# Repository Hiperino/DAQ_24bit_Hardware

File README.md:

# DAQ_24bit
Simple 4 channel 24bit USB DAQ
Uses ADS122U04 ADC and MCP2200 UART/GPIO - USB converter. No Dedicated uC.
4 Input channels with 4 ranges (+- 1V, 2V, 10V, 25V) and 2 current output channels.

Project for fun and curiosity with a purpose to make a simple yte precise USB DAQ without a dedicated controller requireig firmware.

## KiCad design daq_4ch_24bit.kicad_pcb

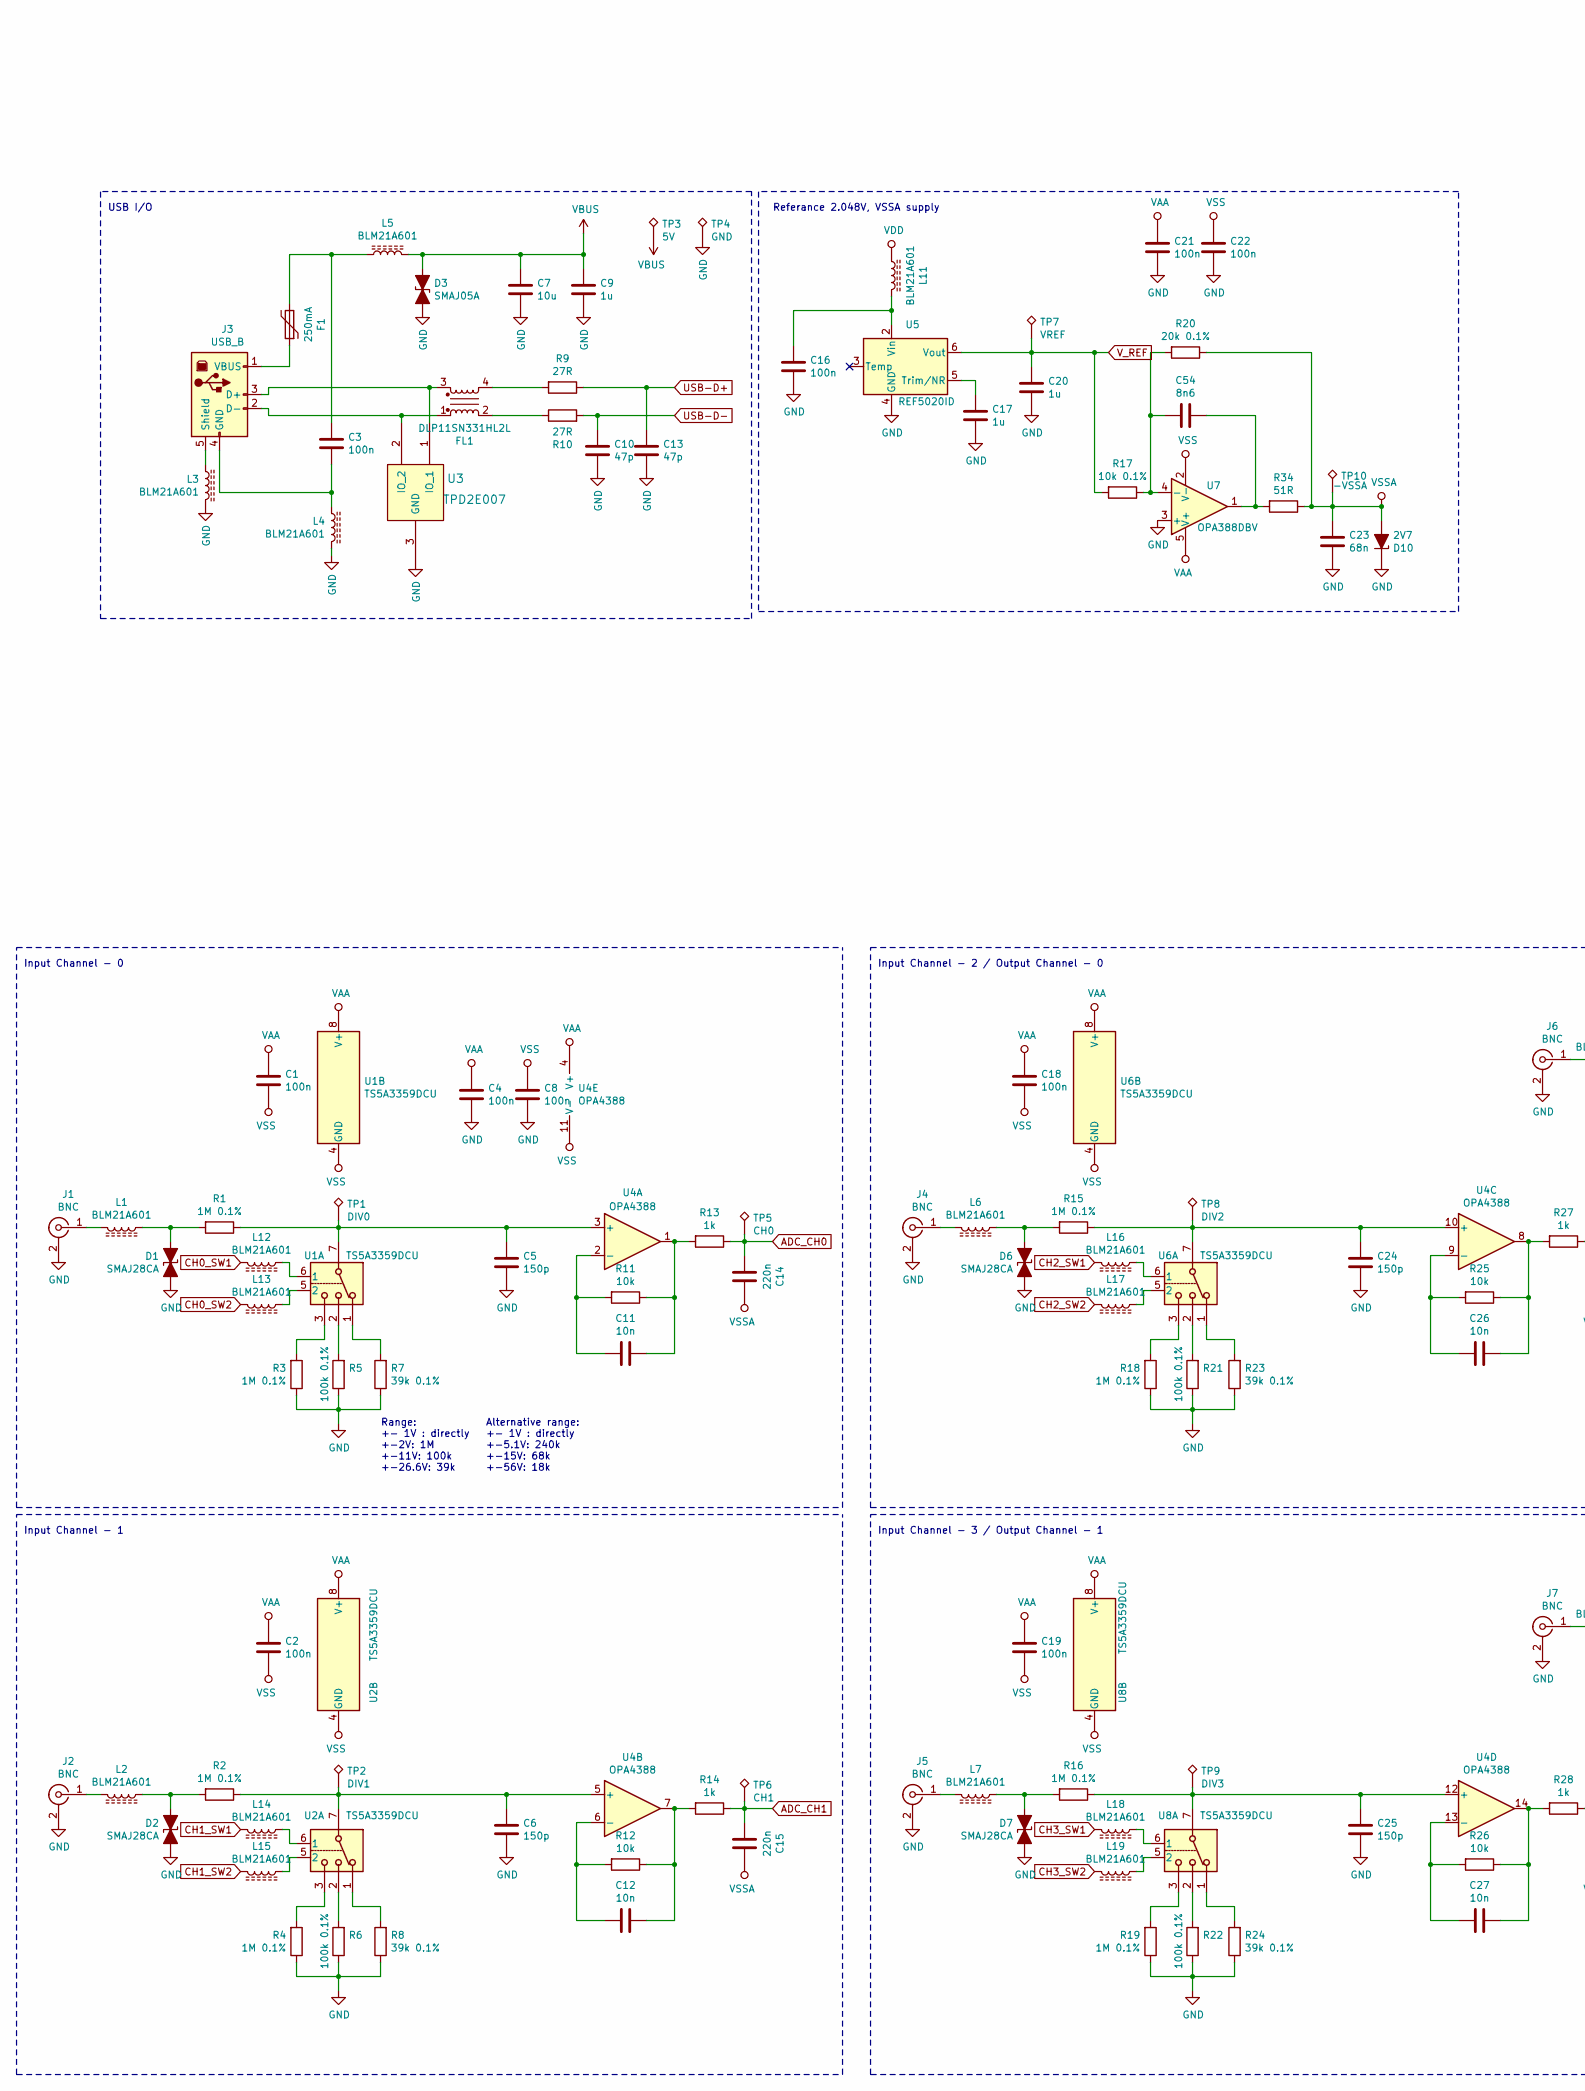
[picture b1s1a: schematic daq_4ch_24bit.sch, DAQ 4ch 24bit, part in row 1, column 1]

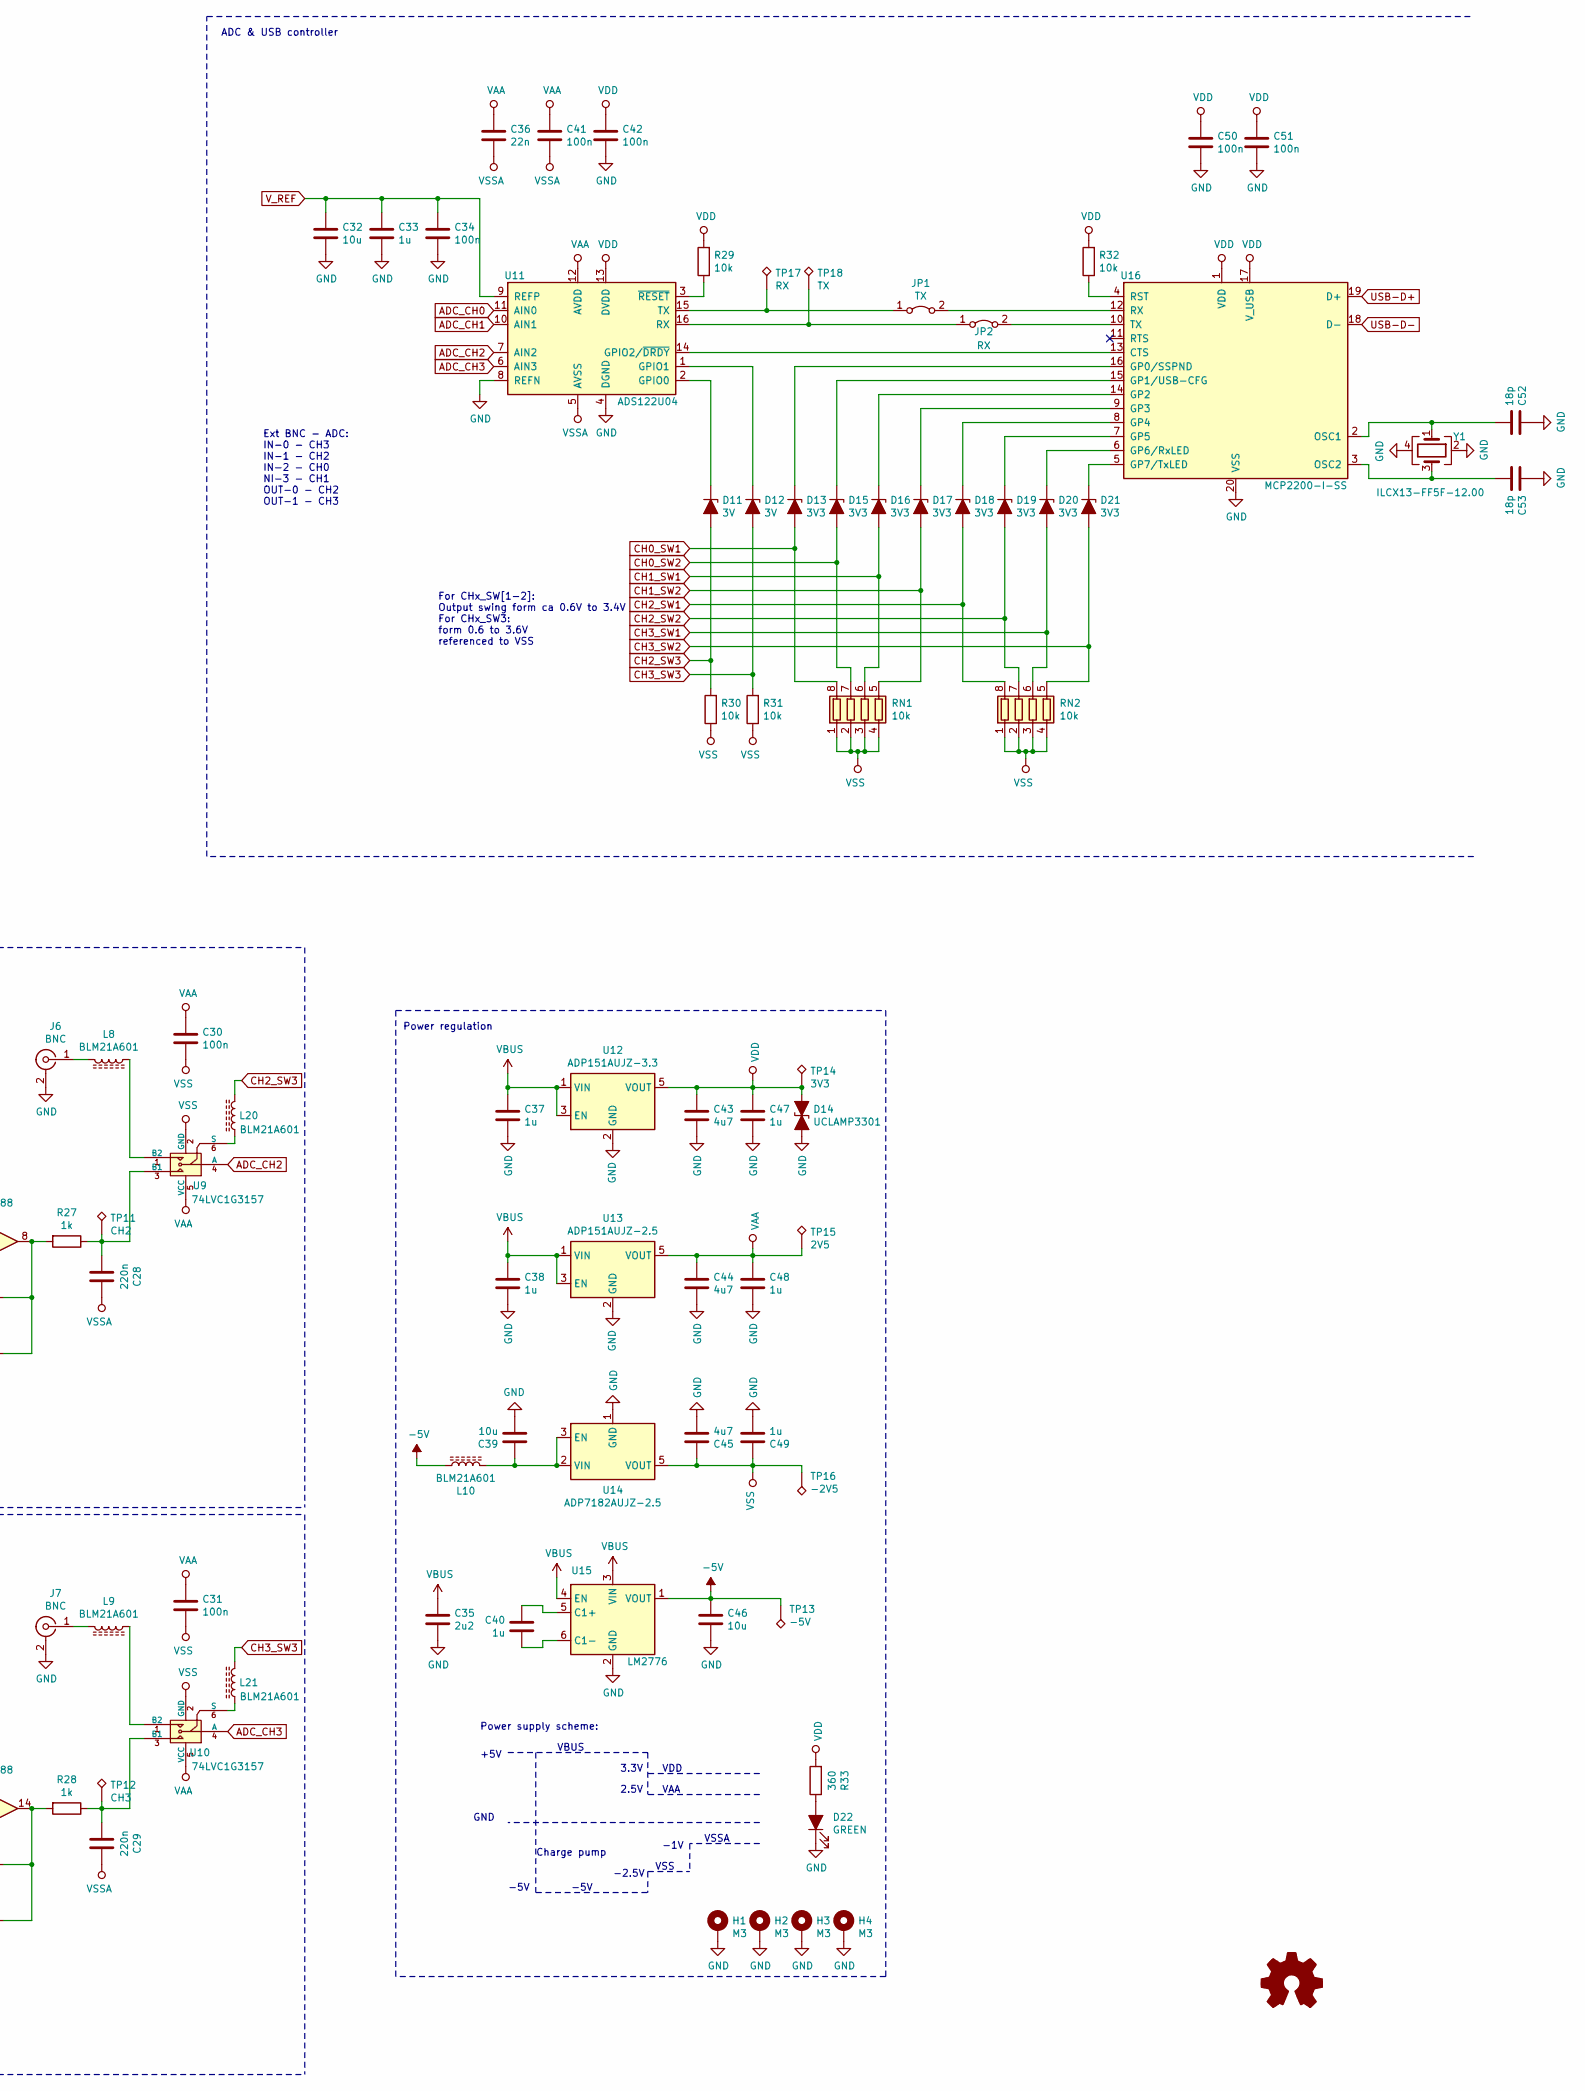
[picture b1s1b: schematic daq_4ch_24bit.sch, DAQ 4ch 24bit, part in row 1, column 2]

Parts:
C1, C2, C3, C4, C8, C16, C18, C19, C21, C22, C30, C31, C34, C41, C42, C50, C51: 100n; C_0805_2012Metric
C5, C6, C24, C25: 150p; C_0805_2012Metric
C7, C32, C39, C46: 10u; C_0805_2012Metric
C9, C17, C20, C33, C37, C38, C40, C47, C48, C49: 1u; C_0805_2012Metric
C10, C13: 47p; C_0805_2012Metric
C11, C12, C26, C27: 10n; C_0805_2012Metric
C14, C15, C28, C29: 220n; C_0805_2012Metric
C23: 68n; C_0805_2012Metric
C35: 2u2; C_0805_2012Metric
C36: 22n; C_0805_2012Metric
C43, C44, C45: 4u7; C_0805_2012Metric
C52, C53: 18p; C_0805_2012Metric
C54: 8n6; C_0805_2012Metric
D1, D2, D6, D7: SMAJ28CA; D_SMA
D3: SMAJ05A; D_SMA
D10: 2V7; D_SOD-123
D11, D12: 3V; D_SOD-123
D13, D15, D16, D17, D18, D19, D20, D21: 3V3; D_SOD-123
D14: UCLAMP3301; D_SOD-323
D22: GREEN; LED_D5.0mm_Horizontal_O1.27mm_Z3.0mm
F1: 250mA; Fuse_1206_3216Metric
FL1: DLP11SN331HL2L; DLP11x
H1, H2, H3, H4: M3
J1, J2, J4, J5, J6, J7: BNC; BNC_Amphenol_B6252HB-NPP3G-50_Horizontal
J3: USB_B; USB_B_OST_USB-B1HSxx_Horizontal
JP1: TX; SolderJumper-2_P1.3mm_Open_TrianglePad1.0x1.5mm
JP2: RX; SolderJumper-2_P1.3mm_Open_TrianglePad1.0x1.5mm
L1, L2, L3, L4, L5, L6, L7, L8, L9, L10, L11, L12, L13, L14, L15, L16, L17, L18, L19, L20, L21: BLM21A601; L_0805_2012Metric
R1, R2, R3, R4, R15, R16, R18, R19: 1M 0.1%; R_0805_2012Metric
R5, R6, R21, R22: 100k 0.1%; R_0805_2012Metric
R7, R8, R23, R24: 39k 0.1%; R_0805_2012Metric
R9, R10: 27R; R_0805_2012Metric
R11, R12, R25, R26, R29, R30, R31, R32: 10k; R_0805_2012Metric
R13, R14, R27, R28: 1k; R_0805_2012Metric
R17: 10k 0.1%; R_0805_2012Metric
R20: 20k 0.1%; R_0805_2012Metric
R33: 360; R_0805_2012Metric
R34: 51R; R_0805_2012Metric
RN1, RN2: 10k; R_Array_Convex_4x0603
TP1: DIV0; TestPoint_Pad_D1.5mm
TP2: DIV1; TestPoint_Pad_D1.5mm
TP3: 5V; TestPoint_THTPad_2.5x2.5mm_Drill1.2mm
TP4: GND; TestPoint_THTPad_2.5x2.5mm_Drill1.2mm
TP5: CH0; TestPoint_Pad_D1.5mm
TP6: CH1; TestPoint_Pad_D1.5mm
TP7: VREF; TestPoint_Pad_D1.5mm
TP8: DIV2; TestPoint_Pad_D1.5mm
TP9: DIV3; TestPoint_Pad_D1.5mm
TP10: -VSSA; TestPoint_THTPad_2.5x2.5mm_Drill1.2mm
TP11: CH2; TestPoint_Pad_D1.5mm
TP12: CH3; TestPoint_Pad_D1.5mm
TP13: -5V; TestPoint_THTPad_2.5x2.5mm_Drill1.2mm
TP14: 3V3; TestPoint_THTPad_2.5x2.5mm_Drill1.2mm
TP15: 2V5; TestPoint_THTPad_2.5x2.5mm_Drill1.2mm
TP16: -2V5; TestPoint_THTPad_2.5x2.5mm_Drill1.2mm
TP17: RX; TestPoint_THTPad_2.5x2.5mm_Drill1.2mm
TP18: TX; TestPoint_THTPad_2.5x2.5mm_Drill1.2mm
U1, U2, U6, U8: TS5A3359DCU; VSSOP-8_2.3x2mm_P0.5mm
U3: TPD2E007; SOT-323_SC-70
U4: OPA4388; SOIC-14_3.9x8.7mm_P1.27mm
U5: REF5020ID; SOIC-8_3.9x4.9mm_P1.27mm
U7: OPA388DBV; SOT-23-5
U9, U10: 74LVC1G3157; SOT-23-6
U11: ADS122U04; TSSOP-16_4.4x5mm_P0.65mm
U12: ADP151AUJZ-3.3; SOT-23-5
U13: ADP151AUJZ-2.5; SOT-23-5
U14: ADP7182AUJZ-2.5; TSOT-23-5
U15: LM2776; SOT-23-6
U16: MCP2200-I-SS; SSOP-20_5.3x7.2mm_P0.65mm
Y1: ILCX13-FF5F-12.00; Crystal_SMD_3225-4Pin_3.2x2.5mm

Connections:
-5V: C46.1, L10.2, TP13.1, U15.1 (VOUT)
ADC_CH0: C14.2, R13.1, TP5.1, U11.11 (AIN0)
ADC_CH1: C15.2, R14.1, TP6.1, U11.10 (AIN1)
ADC_CH2: U9.4 (A), U11.7 (AIN2)
ADC_CH3: U10.4 (A), U11.6 (AIN3)
CH0_SW1: D13.2 (A), L12.1, RN1.8 (R1.2)
CH0_SW2: D15.2 (A), L13.1, RN1.7 (R2.2)
CH1_SW1: D16.2 (A), L14.1, RN1.6 (R3.2)
CH1_SW2: D17.2 (A), L15.1, RN1.5 (R4.2)
CH2_SW1: D18.2 (A), L16.1, RN2.8 (R1.2)
CH2_SW2: D19.2 (A), L17.1, RN2.7 (R2.2)
CH2_SW3: D11.2 (A), L20.1, R30.2
CH3_SW1: D20.2 (A), L18.1, RN2.6 (R3.2)
CH3_SW2: D21.2 (A), L19.1, RN2.5 (R4.2)
CH3_SW3: D12.2 (A), L21.1, R31.2
GND: C4.2, C5.2, C6.2, C7.2, C8.2, C9.2, C10.2, C13.2, C16.2, C17.2, C20.2, C21.2, C22.2, C23.2, C24.2, C25.2, C32.2, C33.2, C34.2, C35.2, C37.2, C38.2, C39.2, C42.2, C43.2, C44.2, C45.2, C46.2, C47.2, C48.2, C49.2, C50.2, C51.2, C52.1, C53.1, D1.2 (A2), D2.2 (A2), D3.2 (A2), D6.2 (A2), D7.2 (A2), D10.1 (K), D14.2 (A2), D22.1 (K), H1.1, H2.1, H3.1, H4.1, J1.2 (Ext), J2.2 (Ext), J4.2 (Ext), J5.2 (Ext), J6.2 (Ext), J7.2 (Ext), L3.1, L4.1, R3.1, R4.1, R5.1, R6.1, R7.1, R8.1, R18.1, R19.1, R21.1, R22.1, R23.1, R24.1, TP4.1, U3.3 (GND), U5.4 (GND), U7.3 (+), U11.4 (DGND), U11.8 (REFN), U12.2 (GND), U13.2 (GND), U14.1 (GND), U15.2 (GND), U16.20 (VSS), Y1.2, Y1.4
unnamed: C3.1, F1.2, L5.2
unnamed: C3.2, J3.4 (GND), L4.2
unnamed: C5.1, R1.1, TP1.1, U1.7, U4.3 (+)
unnamed: C6.1, R2.1, TP2.1, U2.7, U4.5 (+)
unnamed: C11.1, R11.1, R13.2, U4.1
unnamed: C11.2, R11.2, U4.2 (-)
unnamed: C12.1, R12.1, R14.2, U4.7
unnamed: C12.2, R12.2, U4.6 (-)
unnamed: C16.1, L11.1, U5.2 (Vin)
unnamed: C17.1, U5.5 (Trim/NR)
unnamed: C24.1, R15.1, TP8.1, U4.10 (+), U6.7
unnamed: C25.1, R16.1, TP9.1, U4.12 (+), U8.7
unnamed: C26.1, R25.1, R27.2, U4.8
unnamed: C26.2, R25.2, U4.9 (-)
unnamed: C27.1, R26.1, R28.2, U4.14
unnamed: C27.2, R26.2, U4.13 (-)
unnamed: C28.2, R27.1, TP11.1, U9.3 (B1)
unnamed: C29.2, R28.1, TP12.1, U10.3 (B1)
unnamed: C39.1, L10.1, U14.2 (VIN), U14.3 (EN)
unnamed: C40.1, U15.5 (C1+)
unnamed: C40.2, U15.6 (C1-)
unnamed: C52.2, U16.2 (OSC1), Y1.1
unnamed: C53.2, U16.3 (OSC2), Y1.3
unnamed: C54.1, R34.2, U7.1
unnamed: C54.2, R17.1, R20.2, U7.4 (-)
unnamed: D1.1 (A1), L1.2, R1.2
unnamed: D2.1 (A1), L2.2, R2.2
unnamed: D6.1 (A1), L6.2, R15.2
unnamed: D7.1 (A1), L7.2, R16.2
unnamed: D11.1 (K), U11.2 (GPIO0)
unnamed: D12.1 (K), U11.1 (GPIO1)
unnamed: D13.1 (K), U16.16 (GP0/SSPND)
unnamed: D15.1 (K), U16.15 (GP1/USB-CFG)
unnamed: D16.1 (K), U16.14 (GP2)
unnamed: D17.1 (K), U16.9 (GP3)
unnamed: D18.1 (K), U16.8 (GP4)
unnamed: D19.1 (K), U16.7 (GP5)
unnamed: D20.1 (K), U16.6 (GP6/RxLED)
unnamed: D21.1 (K), U16.5 (GP7/TxLED)
unnamed: D22.2 (A), R33.1
unnamed: F1.1, J3.1 (VBUS)
unnamed: FL1.1, J3.2 (D-), U3.2 (IO_2)
unnamed: FL1.2, R10.1
unnamed: FL1.3, J3.3 (D+), U3.1 (IO_1)
unnamed: FL1.4, R9.2
unnamed: J1.1 (In), L1.1
unnamed: J2.1 (In), L2.1
unnamed: J3.5 (Shield), L3.2
unnamed: J4.1 (In), L6.1
unnamed: J5.1 (In), L7.1
unnamed: J6.1 (In), L8.1
unnamed: J7.1 (In), L9.1
unnamed: JP1.1 (A), TP17.1, U11.15 (TX)
unnamed: JP1.2 (B), U16.12 (RX)
unnamed: JP2.1 (A), TP18.1, U11.16 (RX)
unnamed: JP2.2 (B), U16.10 (TX)
unnamed: L8.2, U9.1 (B2)
unnamed: L9.2, U10.1 (B2)
unnamed: L12.2, U1.6 (1)
unnamed: L13.2, U1.5 (2)
unnamed: L14.2, U2.6 (1)
unnamed: L15.2, U2.5 (2)
unnamed: L16.2, U6.6 (1)
unnamed: L17.2, U6.5 (2)
unnamed: L18.2, U8.6 (1)
unnamed: L19.2, U8.5 (2)
unnamed: L20.2, U9.6 (S)
unnamed: L21.2, U10.6 (S)
unnamed: R3.2, U1.3
unnamed: R4.2, U2.3
unnamed: R5.2, U1.2
unnamed: R6.2, U2.2
unnamed: R7.2, U1.1
unnamed: R8.2, U2.1
unnamed: R18.2, U6.3
unnamed: R19.2, U8.3
unnamed: R21.2, U6.2
unnamed: R22.2, U8.2
unnamed: R23.2, U6.1
unnamed: R24.2, U8.1
unnamed: R29.1, U11.3 (~RESET)
unnamed: R32.1, U16.4 (RST)
unnamed: U11.14 (GPIO2/~DRDY), U16.13 (CTS)
USB-D+: C13.1, R9.1, U16.19 (D+)
USB-D-: C10.1, R10.2, U16.18 (D-)
VAA: C1.1, C2.1, C4.1, C18.1, C19.1, C21.1, C30.1, C31.1, C36.1, C41.1, C44.1, C48.1, TP15.1, U1.8 (V+), U2.8 (V+), U4.4 (V+), U6.8 (V+), U7.5 (V+), U8.8 (V+), U9.5 (VCC), U10.5 (VCC), U11.12 (AVDD), U13.5 (VOUT)
VBUS: C7.1, C9.1, C35.1, C37.1, C38.1, D3.1 (A1), L5.1, TP3.1, U12.1 (VIN), U12.3 (EN), U13.1 (VIN), U13.3 (EN), U15.3 (VIN), U15.4 (EN)
VDD: C42.1, C43.1, C47.1, C50.1, C51.1, D14.1 (A1), L11.2, R29.2, R32.2, R33.2, TP14.1, U11.13 (DVDD), U12.5 (VOUT), U16.1 (VDD), U16.17 (V_USB)
VSS: C1.2, C2.2, C8.1, C18.2, C19.2, C22.1, C30.2, C31.2, C45.1, C49.1, R30.1, R31.1, RN1.1 (R1.1), RN1.2 (R2.1), RN1.3 (R3.1), RN1.4 (R4.1), RN2.1 (R1.1), RN2.2 (R2.1), RN2.3 (R3.1), RN2.4 (R4.1), TP16.1, U1.4 (GND), U2.4 (GND), U4.11 (V-), U6.4 (GND), U7.2 (V-), U8.4 (GND), U9.2 (GND), U10.2 (GND), U14.5 (VOUT)
VSSA: C14.1, C15.1, C23.1, C28.1, C29.1, C36.2, C41.2, D10.2 (A), R20.1, R34.1, TP10.1, U11.5 (AVSS)
V_REF: C20.1, C32.1, C33.1, C34.1, R17.2, TP7.1, U5.6 (Vout), U11.9 (REFP)

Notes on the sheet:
Range: +- 1V : directly +-2V: 1M +-11V: 100k +-26.6V: 39k
+5V
GND
-5V
Charge pump
3.3V
-2.5V
-1V
2.5V
Referance 2.048V, VSSA supply
Input Channel - 0
Input Channel - 1
Input Channel - 2 / Output Channel - 0
Input Channel - 3 / Output Channel - 1
USB I/O
ADC & USB controller
VBUS
VDD
VAA
VSS
VSSA
Power regulation
For CHx_SW[1-2]: Output swing form ca 0.6V to 3.4V For CHx_SW3: form 0.6 to 3.6V referenced to VSS
Ext BNC - ADC: IN-0 - CH3 IN-1 - CH2 IN-2 - CH0 NI-3 - CH1 OUT-0 - CH2 OUT-1 - CH3
Alternative range: +- 1V : directly +-5.1V: 240k +-15V: 68k +-56V: 18k
Power supply scheme:

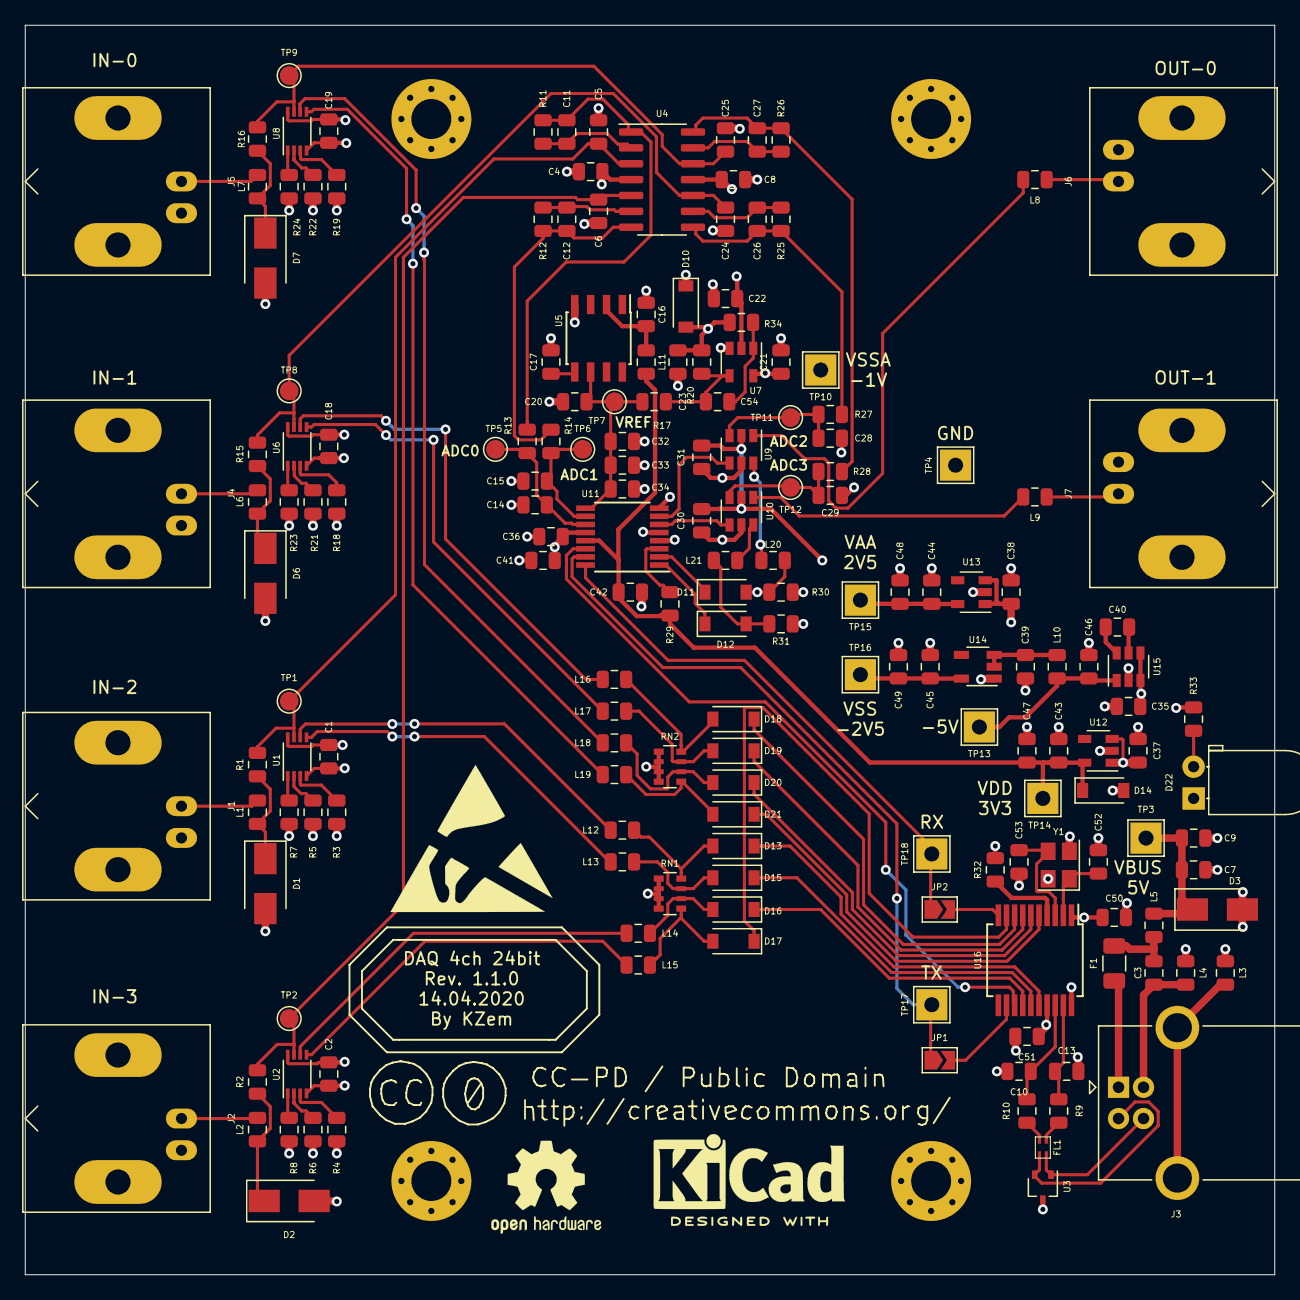
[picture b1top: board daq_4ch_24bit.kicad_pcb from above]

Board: 4 copper layers, 100.0 x 100.0 mm, 179 parts (0 on the bottom side), 107 nets.

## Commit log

2020-04-14 Initial commit.
2020-04-14 Added photos.
